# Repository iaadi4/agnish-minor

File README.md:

# pcbassist: prompt-driven PCB design assistant

> **AI-GENERATED DESIGN PLANS ARE NOT VERIFIED FOR FABRICATION.** Everything this tool
> produces must be reviewed and signed off by a qualified electronics engineer before any
> fabrication, assembly or use. The disclaimer is embedded in every output file.

`pcbassist` turns a natural-language hardware requirement into a structured, reviewable
PCB design plan: requirements, architecture, a bill of materials, a pin-level netlist,
electrical and mechanical constraints, a deterministic placement, routing guidance, and
the results of the checks (ERC, power budget, DFM and KiCad DRC). It exports
KiCad 8 files (`.net`, `.kicad_pro`, `.kicad_sch`, `.kicad_pcb`), a BOM CSV and a
`report.md`. A human reviews it through comments, approve/reject/edit/lock decisions and
partial regeneration with a diff, either on the CLI or in a local web UI.

## The core principle: the LLM proposes, deterministic code verifies

| Concern | Owner |
|---|---|
| Interpreting the prompt; assumptions, open questions, conflicts | LLM, output validated against the `Requirements` schema |
| Block architecture | LLM (`Architecture`), coverage checked in code |
| Choosing **every part**, support passives included: a curated MPN, or any of the 21,700 stock KiCad 8 symbols with an exact footprint | LLM (`PartsManifest`) with lookup tools; **every** symbol, footprint and pin-to-pad match checked against the bundled KiCad index |
| The pin-level netlist (`REF.PIN` endpoints, no-connects with reasons, rails) | LLM (`NetlistIntent`) from a pin dossier of real pins; **every** endpoint, pin, short and rail checked, then ERC and the power budget |
| Repairing what the checks find | LLM, in a loop: each submission comes back with the problems to fix until it validates |
| Constraints, IPC-2221 trace widths, outline, holes, placement, routing guidance | **Deterministic** |
| ERC, power budget, DFM, DRC | **Deterministic** Python plus `kicad-cli` |

This "intent engine" follows the design of
[copperhead](https://github.com/copperheadhq/copperhead): the model authors *intent* (parts
and connections), never geometry, and nothing is accepted until deterministic tools agree.
The model never sees an invented pin: its pin dossier, the `symbol_pins` tool and every
validator message come from the KiCad libraries. A part outside the curated library gets
its pins from its KiCad symbol and is flagged `LIB-KICAD-ONLY` (MPN, package match and
ratings unverified); any ratings the model states are flagged `LIB-CLAIMED-RATINGS`.
Datasheet URLs come only from curated data or KiCad symbol metadata, never from the model.

`--engine synth` keeps the original rule-based path: the LLM picks curated MPNs and a
deterministic synthesizer wires them (only the subcircuits it has rules for).

## Quick start

```bash
uv sync
# Offline: hand-authored fixtures stand in for the model (see "Mock mode" below)
uv run pcbassist generate -f examples/iot_env_sensor/prompt.txt --out out/iot --mock-llm
# Live: Anthropic API (model from PCBASSIST_MODEL, default claude-sonnet-5-5)
export ANTHROPIC_API_KEY=...
uv run pcbassist generate "USB-C powered CO2 sensor with an e-paper display" --out out/co2

# Look up what the model can use (the bundled KiCad 8 index)
uv run pcbassist kicad search INA226
uv run pcbassist kicad pins Sensor_Energy:INA226
uv run pcbassist kicad footprint Package_SO:VSSOP-10_3x3mm_P0.5mm
```

`out/iot/` is a **session**:

```
plan.json          latest plan        plan.v1.json, plan.v2.json ...  one file per version
audit.jsonl        every LLM prompt/response and review decision (API keys redacted)
v1/                board.kicad_pcb  board.kicad_sch  board.kicad_pro  board.net
                   bom.csv  report.md  drc.json (when kicad-cli ran)
```

`make demo` generates all five examples plus a refinement into `out/demo/`;
`make serve-demo` opens them in the review UI at http://127.0.0.1:8000.

## Pipeline

```
prompt -> requirements -> architecture -> parts ("components") -> netlist -> constraints
  (LLM)       (LLM)           (LLM + tools, validated)   (LLM + tools, validated + ERC)
                                     ^------ part-level ERC problems loop back ------'
       -> placement -> routing -> checks -> exports
           (rules)      (rules)   ERC/power/DFM/library (+ KiCad DRC on export)
```

**Parts and netlist stages** run as a tool loop on the Anthropic Messages API. The model
can call `search_parts` (curated library), `search_symbols`, `symbol_pins`,
`check_footprints` and `search_footprints` (the KiCad index), and submits with `submit`.
Each submission is parsed with Pydantic and then checked by `pipeline/intent.py`:

* parts: one entry per refdes, value is a value not prose, the block exists, the KiCad
  symbol exists (with "did you mean" / "installed as" suggestions), the footprint exists,
  every symbol pin is a footprint pad, MPN present for active parts, curated parts keep
  their verified symbol and footprint, locked parts stay, rejected parts stay out;
* netlist: every endpoint is a real `REF.PIN` (the error lists the part's pins, or maps
  a pin *name* to its number), no pin in two nets, every pin of every part is in a net or
  a no-connect with a reason, power inputs and grounds are never no-connect, every rail
  has a voltage; then ERC (decoupling, pull-ups, USB-C CC, flyback, LED resistor, driver
  conflicts, supply range, ground pins) and the power budget.

Problems are sent back as `is_error` tool results, up to 5 submissions per stage. Problems
that rewiring cannot fix (a missing decoupling capacitor or pull-up) send the parts stage
round again with that feedback (up to 2 extra rounds). What is still open at the end is
reported as error findings, never dropped. Tool stages are streamed and use automatic
prompt caching.

The requirements and architecture stages put the JSON Schema of their output model in
the system prompt and validate the reply with Pydantic. Unknown keys are rejected (`extra="forbid"`). On a
validation error the errors are sent back and the model retries, up to 3 attempts in
total. A truncated reply counts as invalid. Refusals and API failures surface as typed
`LLMError`s with readable messages.

## Reviewing and iterating

```bash
pcbassist review comment  out/iot -t component:U3 -m "antenna clearance vs enclosure?"
pcbassist review approve  out/iot -t component:U3
pcbassist review lock     out/iot -t component:U2         # kept verbatim on regeneration
pcbassist review reject   out/iot -t component:D2         # avoided on the next refine
pcbassist review edit     out/iot -t placement:R1 --set x_mm=20 --set y_mm=12   # new version
pcbassist refine out/iot --mock-llm -f "Replace the SHT40 with a BME280 so we also get barometric pressure."
pcbassist diff out/iot/plan.v1.json out/iot/plan.v2.json
pcbassist review approve  out/iot -t 'plan:*'             # refuses while checks FAIL (unless --force)
pcbassist check out/iot                                   # exit 1 on FAIL
```

`refine` picks the earliest stage the feedback affects, using deterministic rules:

| Feedback | Restarts at |
|---|---|
| Names a library part, or "replace / instead / swap / use a..." | components |
| "move / place / closer / rotate..." | placement |
| "route / trace / ground plane / stackup..." | routing |
| "60 x 40 mm", "4 layers", "mounting hole", "fab profile" | constraints |
| "connect / wire / pull-up / tie / strap / GPIO / pinout..." | netlist (components with `--engine synth`) |
| Anything else | requirements |

Only that stage and the ones after it are regenerated. Numeric directives (board size,
layer count) are applied directly. Locked and edited parts are carried over and the LLM
is told about them; a rejected MPN is refused by the parts validator, and if the model
proposes it again anyway it stays flagged `rejected` with a `SEL-REJECTED-AGAIN` error. Approvals carry over to parts that did not
change. A locked net that changes produces an error. Each refinement is saved as a new
version, and `diff` reports what changed: parts, nets, rails, outline, moved parts,
findings and the status change.

`pcbassist serve --sessions out` starts a FastAPI app with a single static page: findings,
components with approve/reject/lock/comment buttons, nets, a board view (outline, zones,
antenna keepout, courtyards), the power tree, refinement, a diff between any two versions,
and file downloads. Its REST API is under `/api/sessions/...`.

## Checks

| Group | Rules (finding id prefix) |
|---|---|
| ERC | `ERC-UNCONNECTED` (every pin on a net or an explicit NC with a reason), `ERC-MULTI-NET`, `ERC-NC-CONNECTED`, `ERC-SINGLE-PIN-NET`, `ERC-DRIVER-CONFLICT`, `ERC-POWER-UNDRIVEN`, `ERC-GROUND-PIN`, `ERC-SUPPLY-RANGE`, `ERC-DECOUPLING`, `ERC-I2C-PULLUP`, `ERC-I2C-ADDRESS`, `ERC-USB-ESD`, `ERC-USB-CC`, `ERC-FLOATING-INPUT`, `ERC-FLYBACK`, `ERC-LED-RESISTOR`, `ERC-CAP-VOLTAGE` |
| Power | `PWR-SOURCE`, `PWR-REG-CAPACITY`, `PWR-DROPOUT`, `PWR-REG-INPUT`, `PWR-THERMAL`, `PWR-CHARGE-RATE`, `PWR-BATTERY-LIFE`, `PWR-NO-DATA` |
| DFM / placement | `DFM-PASSIVE-SIZE`, `DFM-PAD-PITCH`, `DFM-DRILL`, `DFM-THT`, `DFM-BGA`, `DFM-NETCLASS`, `DFM-COURTYARD-OVERLAP`, `DFM-OUTSIDE-BOARD`, `DFM-EDGE-CLEARANCE`, `DFM-KEEPOUT`, `DFM-UNPLACED`, `DFM-DECOUPLING-DISTANCE`, `DFM-CONNECTOR-EDGE`, `DFM-MIXED-ASSEMBLY` |
| Library | `LIB-UNVERIFIED`, `LIB-FOOTPRINT`, `LIB-LOW-CONFIDENCE`, `LIB-NO-DATASHEET` |
| KiCad DRC | `DRC-<type>` from `kicad-cli pcb drc`. Unrouted connections and silkscreen findings are expected on an unrouted, auto-placed board, so they are reported as info. Errors that lie entirely inside one library footprint (for example a module's 0.2 mm thermal vias) are reported as warnings. |

Status is `PASS`, `PASS_WITH_WARNINGS` or `FAIL` (any error).

### KiCad DRC

DRC runs during export when `kicad-cli` is available, either from
`PCBASSIST_KICAD_CLI` or from `kicad-cli` on `PATH`. Without KiCad installed:

```bash
export PCBASSIST_KICAD_CLI=$PWD/scripts/kicad-cli-docker   # runs kicad/kicad:8.0.9 in Docker
make test-kicad   # real DRC, plus KiCad's netlist from our schematic compared with the plan's
```

The `Dockerfile` builds on the official KiCad 8 image, so `kicad-cli` is always there:

```bash
docker build -t pcbassist .
docker run --rm -v "$PWD/out:/work/out" pcbassist generate \
  -f /opt/pcbassist/examples/relay_motor_12v/prompt.txt --out out/relay --mock-llm
docker run --rm -p 8000:8000 -v "$PWD/sessions:/work/sessions" pcbassist serve --host 0.0.0.0
```

## Examples

Committed in `examples/<name>/` (prompt and full session output). Regenerate with
`make examples`.

| Example | What it shows | Status |
|---|---|---|
| `iot_env_sensor` | ESP32-C3, USB-C + LiPo charger, LDO, SHT40, battery sense; plus a **v2 refinement** (SHT40 → BME280, see `out/diff_v1_v2.txt`) | PASS_WITH_WARNINGS (thin battery-life margin, LDO dropout at low battery, VBUS at its 500 mA limit) |
| `ble_coin_tag` | nRF52832 module on a CR2032, LIS3DH wake-on-motion, Tag-Connect SWD | PASS_WITH_WARNINGS |
| `relay_motor_12v` | 12 V input with fuse, series diode and TVS; LM2596 buck; LDO; ESP32; DRV8871 H-bridge; relay with FET + flyback; screw terminals; 4 M3 holes | PASS_WITH_WARNINGS |
| `motor_current_monitor` | `relay_motor_12v` plus an **INA226** high-side current monitor on the motor supply. The INA226 is not in the curated library: it comes from the KiCad symbol `Sensor_Energy:INA226` and is wired pin by pin (shunt, VBUS sense, I2C with pull-ups, address straps, decoupling) | PASS_WITH_WARNINGS (`LIB-KICAD-ONLY` for the INA226) |
| `flawed_coin_wifi` | **Intentionally flawed:** Wi-Fi on a coin cell, 3.3 V LDO from 3 V, 5 V relay on 3.3 V, two identical I2C sensors, 15 x 15 mm board, an off-library transistor left unwired | **FAIL**: 14 errors (I2C address clash, supply range, dropout, regulator capacity, source capacity, battery life, board too small...) |

## Mock mode and honesty notes

* **Mock fixtures are not recordings.** The requirements, architecture and (synth-engine)
  selection fixtures are hand-authored; the parts and netlist fixtures are *derived* from
  the synthesizer's design for each example (`scripts/derive_intent_fixtures.py`), plus a
  hand-written INA226 addition for `motor_current_monitor`. Mock mode pushes them through
  the same validators, ERC repair loop and downstream stages as a live run.
* **Mock fixtures in general**: No API key was available while
  this was built. They live in `fixtures/llm/<stage>/<example>.json`, are generated from
  `scripts/author_fixtures.py`, and are written in exactly the JSON shape the live model is
  asked for. Lookup order is an exact prompt hash, then keyword match, then `_default`. A
  non-exact match adds a `MOCK-NEAREST` warning, because the plan then describes the
  nearest example, not your prompt. `generate --record-fixtures DIR` saves live answers as
  new fixtures.
* The live Anthropic path (including the streamed tool loop) is tested against a faked
  SDK client only.
* **KiCad index:** `data/kicad/symbol_index.json.gz` and `footprint_geom.json.gz` (3.6 MB)
  hold every stock KiCad 8.0.9 symbol's pins and every footprint's pads and courtyard,
  built by `scripts/build_kicad_index.py`. Exported boards embed the real footprint file
  when a KiCad library tree is available (`make kicad-libs` copies it out of the Docker
  image), and otherwise a footprint rebuilt from the index (pads + courtyard; KiCad's
  *Update Footprints from Library* restores the graphics).
* **Pin tables** come from the official KiCad symbol libraries. Each pin is cross-checked
  against a pad of the KiCad footprint at seed-build time (`scripts/build_seed.py`). No IC
  pin table was typed by hand. Pins are still the KiCad community's data: verify against
  the datasheet.
* Electrical limits, currents and specs in `data/parts_curated.toml` are curated values
  with a `data_confidence` level. Design rules of thumb (regulator capacitors, ESP32
  strapping pull-ups, DRV8871 ILIM) are in `pipeline/synth.py`, each with its reasoning
  and a "verify" note.
* Relay NO/NC contacts and barrel-jack polarity are not asserted. The report asks the
  engineer to confirm them.

## Configuration

| Variable | Meaning |
|---|---|
| `ANTHROPIC_API_KEY` | Live mode (never logged; redacted in the audit trail) |
| `PCBASSIST_MODEL` | Model id (default `claude-sonnet-5-5`) |
| `PCBASSIST_LLM_FALLBACKS` | `off` disables server-side fallback models |
| `PCBASSIST_LLM_EFFORT` | Optional effort setting passed to the API |
| `PCBASSIST_KICAD_CLI` | Path to `kicad-cli` (or `scripts/kicad-cli-docker`) |
| `PCBASSIST_KICAD_FOOTPRINT_DIR` | KiCad footprint tree for full footprint files (`none` disables) |
| `PCBASSIST_SYMBOL_INDEX`, `PCBASSIST_FOOTPRINT_INDEX` | Override the bundled KiCad index files |
| `PCBASSIST_DATA_DIR`, `PCBASSIST_FIXTURES_DIR` | Override the bundled data / fixtures |

## Development

```bash
make check-all     # ruff, ruff format --check, mypy --strict (core modules), pytest + 80% coverage, library validate
make test-kicad    # the two tests that need real KiCad
make seed          # rebuild the component library from KiCad sources (network)
make fixtures      # regenerate mock fixtures (hand-authored + derived parts/netlist)
make kicad-libs    # copy KiCad 8.0.9 libraries out of Docker into ~/.cache/pcbassist
make kicad-index   # rebuild the bundled symbol/footprint index from them
```

Layout: `schemas/` (Pydantic models + JSON Schema export), `llm/` (client, mock,
structured retry, audit), `library/` (SQLite library, footprint resolver), `kicad/`
(S-expression I/O, footprint geometry), `pipeline/` (stages, synthesizer, constraints,
placement, routing, engine), `checks/`, `export/`, `review/` (sessions, decisions,
refine, diff), `ui/` (FastAPI and a static page). Design decisions and the milestone log
are in [PLAN.md](PLAN.md).

## Known limitations

* No routing (only the ratsnest), single-sided placement and 0° rotations. Edge
  connectors still need rotating so the mating face points off the board.
* The schematic is one flat sheet of generated box symbols with net labels. It is
  correct by construction (KiCad's netlist from it matches the plan) but not a
  hand-drawn schematic.
* The intent engine's quality depends on the model: the validators guarantee that every
  part and pin exists and that ERC/power rules pass, not that the circuit is the best one.
  Ratings of parts outside the curated library are the model's datasheet claims.
* With `--engine synth`, subcircuits exist only for the parts the rules cover (ESP32/nRF52
  modules, MCP73831, fixed LDOs, LM2596-5.0, I2C sensors, USB-C, relays, DRV8871, LEDs,
  buttons, SWD/UART/Qwiic headers, input protection); other parts get power and ground
  only, with a `SYNTH-INCOMPLETE` warning.
* The fab profiles are generic and conservative, not any specific fab's published rules.
* Mains, safety and RF certification are out of scope.

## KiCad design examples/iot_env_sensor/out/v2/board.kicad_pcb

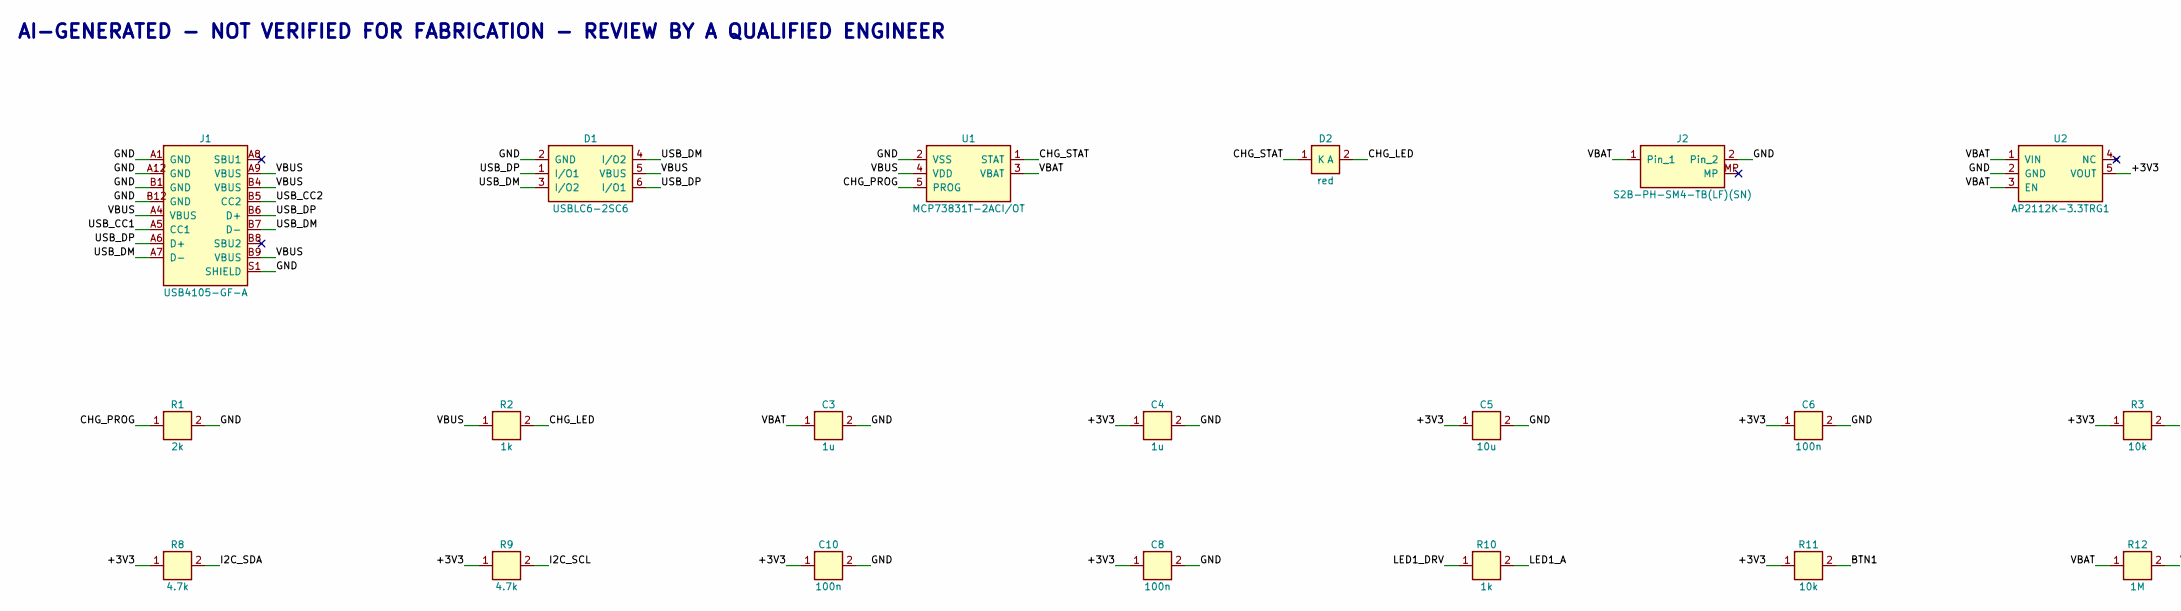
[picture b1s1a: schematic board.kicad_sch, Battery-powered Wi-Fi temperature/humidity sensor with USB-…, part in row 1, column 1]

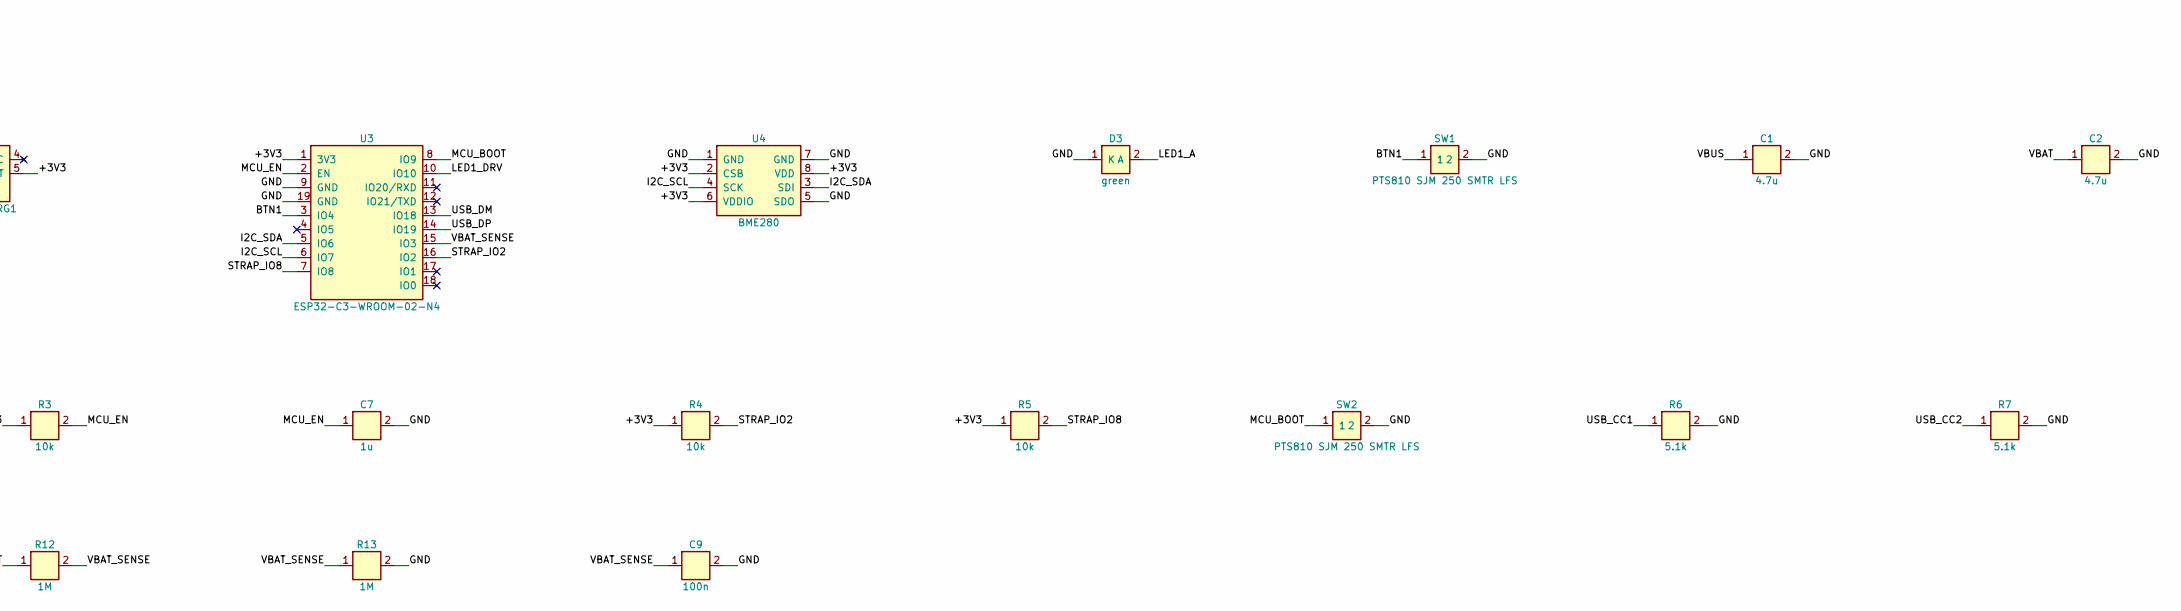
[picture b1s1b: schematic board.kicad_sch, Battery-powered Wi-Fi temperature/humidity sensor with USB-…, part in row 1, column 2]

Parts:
C1, C2: 4.7u; C_0603_1608Metric; MPN GRM188R61A475KE15D
C3, C4, C7: 1u; C_0402_1005Metric; MPN GRM155R61A105KE15D
C5: 10u; C_0603_1608Metric; MPN GRM188R61A106KE69D
C6, C8, C9, C10: 100n; C_0402_1005Metric; MPN GRM155R71C104KA88D
D1: USBLC6-2SC6; SOT-23-6; MPN USBLC6-2SC6
D2: red; LED_0603_1608Metric; MPN LTST-C191KRKT
D3: green; LED_0603_1608Metric; MPN LTST-C191KGKT
J1: USB4105-GF-A; USB_C_Receptacle_GCT_USB4105-xx-A_16P_TopMnt_Horizontal; MPN USB4105-GF-A
J2: S2B-PH-SM4-TB(LF)(SN); JST_PH_S2B-PH-SM4-TB_1x02-1MP_P2.00mm_Horizontal; MPN S2B-PH-SM4-TB(LF)(SN)
R1: 2k; R_0603_1608Metric; MPN RC0603FR-072KL
R2, R10: 1k; R_0402_1005Metric; MPN RC0402FR-071KL
R3, R4, R5, R11: 10k; R_0402_1005Metric; MPN RC0402FR-0710KL
R6, R7: 5.1k; R_0402_1005Metric; MPN RC0402FR-075K1L
R8, R9: 4.7k; R_0402_1005Metric; MPN RC0402FR-074K7L
R12, R13: 1M; R_0402_1005Metric; MPN RC0402FR-071ML
SW1, SW2: PTS810 SJM 250 SMTR LFS; SW_SPST_PTS810; MPN PTS810 SJM 250 SMTR LFS
U1: MCP73831T-2ACI/OT; SOT-23-5; MPN MCP73831T-2ACI/OT
U2: AP2112K-3.3TRG1; SOT-23-5; MPN AP2112K-3.3TRG1
U3: ESP32-C3-WROOM-02-N4; ESP32-C3-WROOM-02; MPN ESP32-C3-WROOM-02-N4
U4: BME280; Bosch_LGA-8_2.5x2.5mm_P0.65mm_ClockwisePinNumbering; MPN BME280

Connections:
+3V3: C4.1, C5.1, C6.1, C8.1, C10.1, R3.1, R4.1, R5.1, R8.1, R9.1, R11.1, U2.5 (VOUT), U3.1 (3V3), U4.2 (CSB), U4.6 (VDDIO), U4.8 (VDD)
BTN1: R11.2, SW1.1, U3.3 (IO4)
CHG_LED: D2.2 (A), R2.2
CHG_PROG: R1.1, U1.5 (PROG)
CHG_STAT: D2.1 (K), U1.1 (STAT)
GND: C1.2, C2.2, C3.2, C4.2, C5.2, C6.2, C7.2, C8.2, C9.2, C10.2, D1.2 (GND), D3.1 (K), J1.A1 (GND), J1.A12 (GND), J1.B1 (GND), J1.B12 (GND), J1.S1 (SHIELD), J2.2, R1.2, R6.2, R7.2, R13.2, SW1.2, SW2.2, U1.2 (VSS), U2.2 (GND), U3.9 (GND), U3.19 (GND), U4.1 (GND), U4.5 (SDO), U4.7 (GND)
I2C_SCL: R9.2, U3.6 (IO7), U4.4 (SCK)
I2C_SDA: R8.2, U3.5 (IO6), U4.3 (SDI)
LED1_A: D3.2 (A), R10.2
LED1_DRV: R10.1, U3.10 (IO10)
MCU_BOOT: SW2.1, U3.8 (IO9)
MCU_EN: C7.1, R3.2, U3.2 (EN)
STRAP_IO2: R4.2, U3.16 (IO2)
STRAP_IO8: R5.2, U3.7 (IO8)
USB_CC1: J1.A5 (CC1), R6.1
USB_CC2: J1.B5 (CC2), R7.1
USB_DM: D1.3 (I/O2), D1.4 (I/O2), J1.A7 (D-), J1.B7 (D-), U3.13 (IO18)
USB_DP: D1.1 (I/O1), D1.6 (I/O1), J1.A6 (D+), J1.B6 (D+), U3.14 (IO19)
VBAT: C2.1, C3.1, J2.1, R12.1, U1.3 (VBAT), U2.1 (VIN), U2.3 (EN)
VBAT_SENSE: C9.1, R12.2, R13.1, U3.15 (IO3)
VBUS: C1.1, D1.5 (VBUS), J1.A4 (VBUS), J1.A9 (VBUS), J1.B4 (VBUS), J1.B9 (VBUS), R2.1, U1.4 (VDD)

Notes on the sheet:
AI-GENERATED - NOT VERIFIED FOR FABRICATION - REVIEW BY A QUALIFIED ENGINEER

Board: 2 copper layers, 34 parts (0 on the bottom side), 21 nets, no tracks yet.

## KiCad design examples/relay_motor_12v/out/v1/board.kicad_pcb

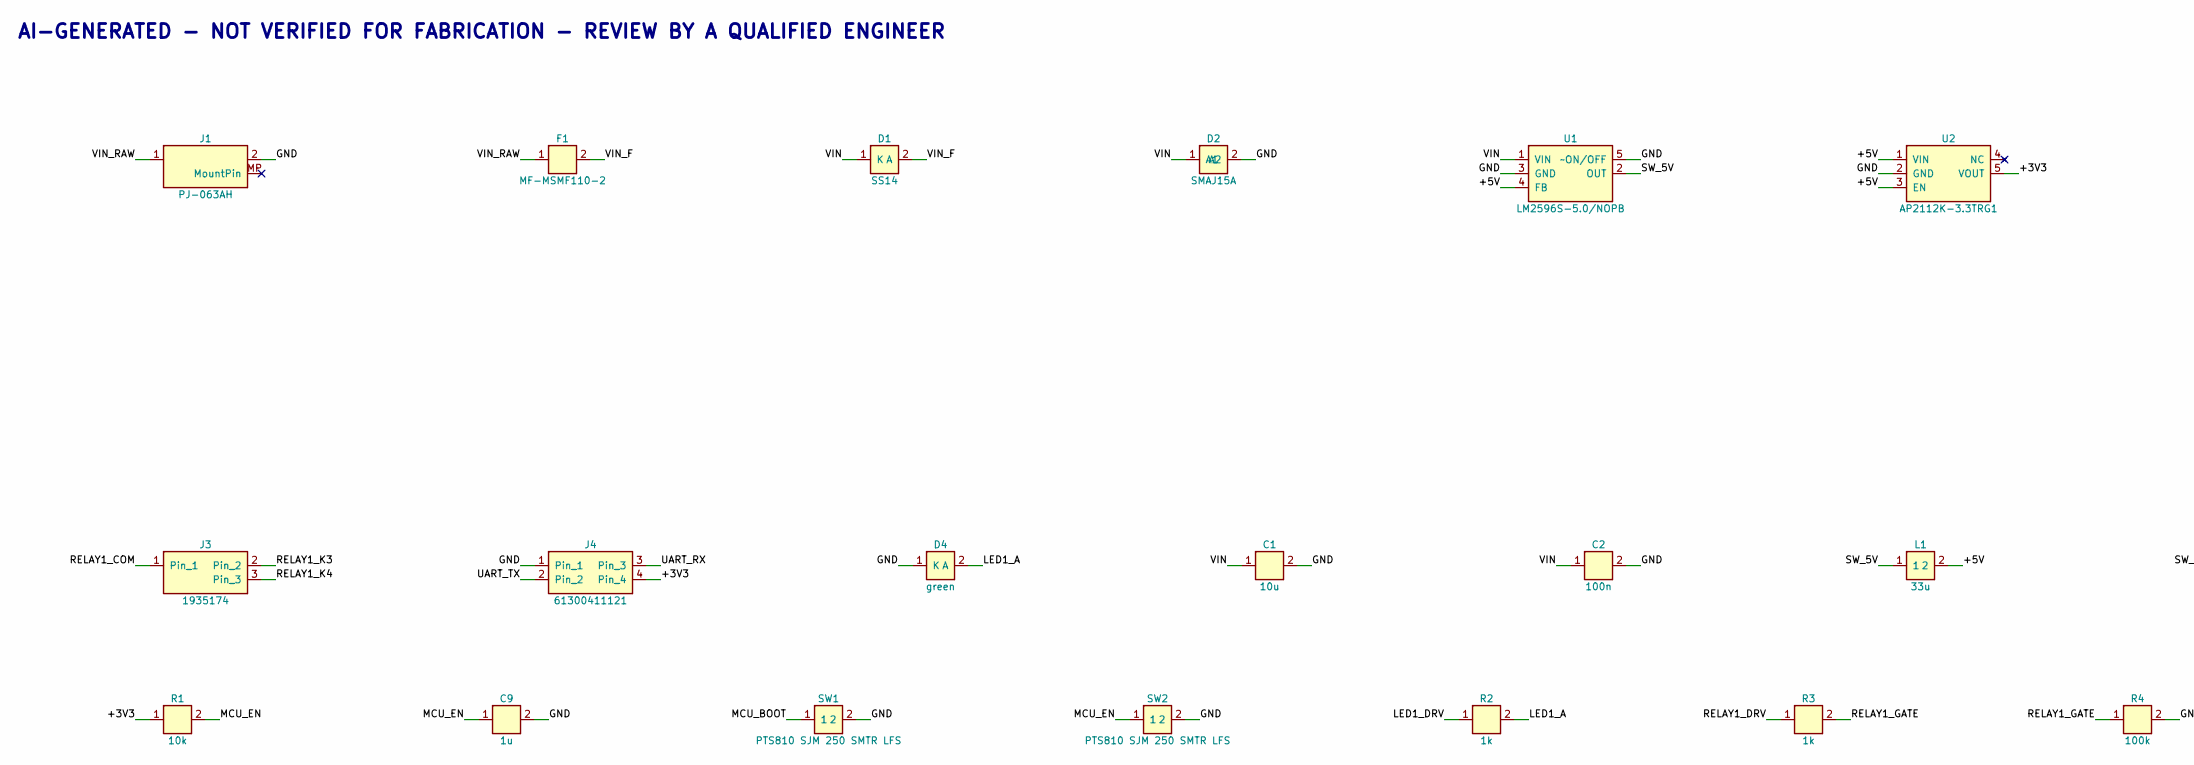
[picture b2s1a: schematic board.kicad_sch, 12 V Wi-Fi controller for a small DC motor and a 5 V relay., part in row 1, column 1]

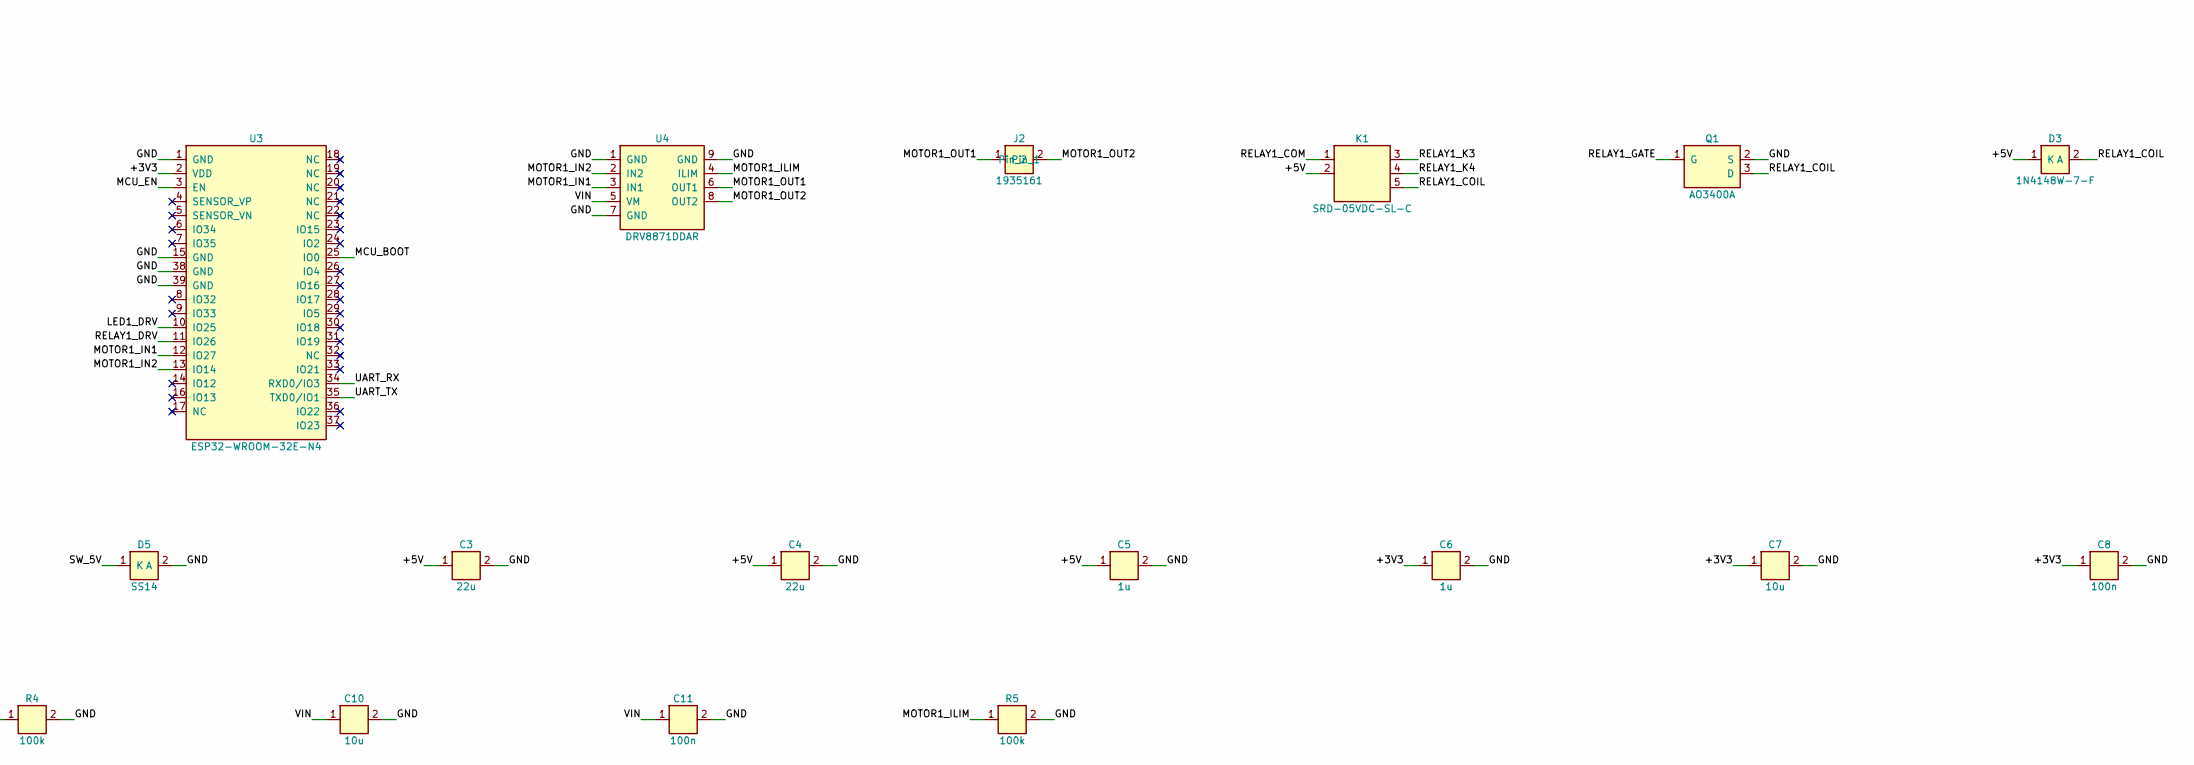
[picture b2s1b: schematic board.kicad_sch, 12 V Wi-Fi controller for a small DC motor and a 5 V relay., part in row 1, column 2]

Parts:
C1, C10: 10u; C_0805_2012Metric; MPN GRM21BR61E106KA73L
C2, C11: 100n; C_0603_1608Metric; MPN GRM188R71H104KA93D
C3, C4: 22u; C_0805_2012Metric; MPN GRM21BR61C226ME44L
C5, C6, C9: 1u; C_0402_1005Metric; MPN GRM155R61A105KE15D
C7: 10u; C_0603_1608Metric; MPN GRM188R61A106KE69D
C8: 100n; C_0402_1005Metric; MPN GRM155R71C104KA88D
D1, D5: SS14; D_SMA; MPN SS14
D2: SMAJ15A; D_SMA; MPN SMAJ15A
D3: 1N4148W-7-F; D_SOD-123; MPN 1N4148W-7-F
D4: green; LED_0603_1608Metric; MPN LTST-C191KGKT
F1: MF-MSMF110-2; Fuse_1812_4532Metric; MPN MF-MSMF110-2
J1: PJ-063AH; BarrelJack_CUI_PJ-063AH_Horizontal; MPN PJ-063AH
J2: 1935161; TerminalBlock_Phoenix_MKDS-1,5-2-5.08_1x02_P5.08mm_Horizont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; MPN 1935161
J3: 1935174; TerminalBlock_Phoenix_MKDS-1,5-3-5.08_1x03_P5.08mm_Horizont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; MPN 1935174
J4: 61300411121; PinHeader_1x04_P2.54mm_Vertical; MPN 61300411121
K1: SRD-05VDC-SL-C; Relay_SPDT_SANYOU_SRD_Series_Form_C; MPN SRD-05VDC-SL-C
L1: 33u; L_Bourns_SRN8040TA; MPN SRN8040TA-330M
Q1: AO3400A; SOT-23; MPN AO3400A
R1: 10k; R_0402_1005Metric; MPN RC0402FR-0710KL
R2, R3: 1k; R_0402_1005Metric; MPN RC0402FR-071KL
R4, R5: 100k; R_0402_1005Metric; MPN RC0402FR-07100KL
SW1, SW2: PTS810 SJM 250 SMTR LFS; SW_SPST_PTS810; MPN PTS810 SJM 250 SMTR LFS
U1: LM2596S-5.0/NOPB; TO-263-5_TabPin3; MPN LM2596S-5.0/NOPB
U2: AP2112K-3.3TRG1; SOT-23-5; MPN AP2112K-3.3TRG1
U3: ESP32-WROOM-32E-N4; ESP32-WROOM-32E; MPN ESP32-WROOM-32E-N4
U4: DRV8871DDAR; Texas_HTSOP-8-1EP_3.9x4.9mm_P1.27mm_EP2.95x4.9mm_Mask2.4x3.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; MPN DRV8871DDAR

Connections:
+3V3: C6.1, C7.1, C8.1, J4.4, R1.1, U2.5 (VOUT), U3.2 (VDD)
+5V: C3.1, C4.1, C5.1, D3.1 (K), K1.2, L1.2, U1.4 (FB), U2.1 (VIN), U2.3 (EN)
GND: C1.2, C2.2, C3.2, C4.2, C5.2, C6.2, C7.2, C8.2, C9.2, C10.2, C11.2, D2.2 (A2), D4.1 (K), D5.2 (A), J1.2, J4.1, Q1.2 (S), R4.2, R5.2, SW1.2, SW2.2, U1.3 (GND), U1.5 (~ON/OFF), U2.2 (GND), U3.1 (GND), U3.15 (GND), U3.38 (GND), U3.39 (GND), U4.1 (GND), U4.7 (GND), U4.9 (GND)
LED1_A: D4.2 (A), R2.2
LED1_DRV: R2.1, U3.10 (IO25)
MCU_BOOT: SW1.1, U3.25 (IO0)
MCU_EN: C9.1, R1.2, SW2.1, U3.3 (EN)
MOTOR1_ILIM: R5.1, U4.4 (ILIM)
MOTOR1_IN1: U3.12 (IO27), U4.3 (IN1)
MOTOR1_IN2: U3.13 (IO14), U4.2 (IN2)
MOTOR1_OUT1: J2.1, U4.6 (OUT1)
MOTOR1_OUT2: J2.2, U4.8 (OUT2)
RELAY1_COIL: D3.2 (A), K1.5, Q1.3 (D)
RELAY1_COM: J3.1, K1.1
RELAY1_DRV: R3.1, U3.11 (IO26)
RELAY1_GATE: Q1.1 (G), R3.2, R4.1
RELAY1_K3: J3.2, K1.3
RELAY1_K4: J3.3, K1.4
SW_5V: D5.1 (K), L1.1, U1.2 (OUT)
UART_RX: J4.3, U3.34 (RXD0/IO3)
UART_TX: J4.2, U3.35 (TXD0/IO1)
VIN: C1.1, C2.1, C10.1, C11.1, D1.1 (K), D2.1 (A1), U1.1 (VIN), U4.5 (VM)
VIN_F: D1.2 (A), F1.2
VIN_RAW: F1.1, J1.1

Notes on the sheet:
AI-GENERATED - NOT VERIFIED FOR FABRICATION - REVIEW BY A QUALIFIED ENGINEER

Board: 2 copper layers, 39 parts (0 on the bottom side), 24 nets, no tracks yet.

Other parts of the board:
H1, H2, H3, H4: MOUNTING-HOLE-M3; MountingHole_3.2mm_M3

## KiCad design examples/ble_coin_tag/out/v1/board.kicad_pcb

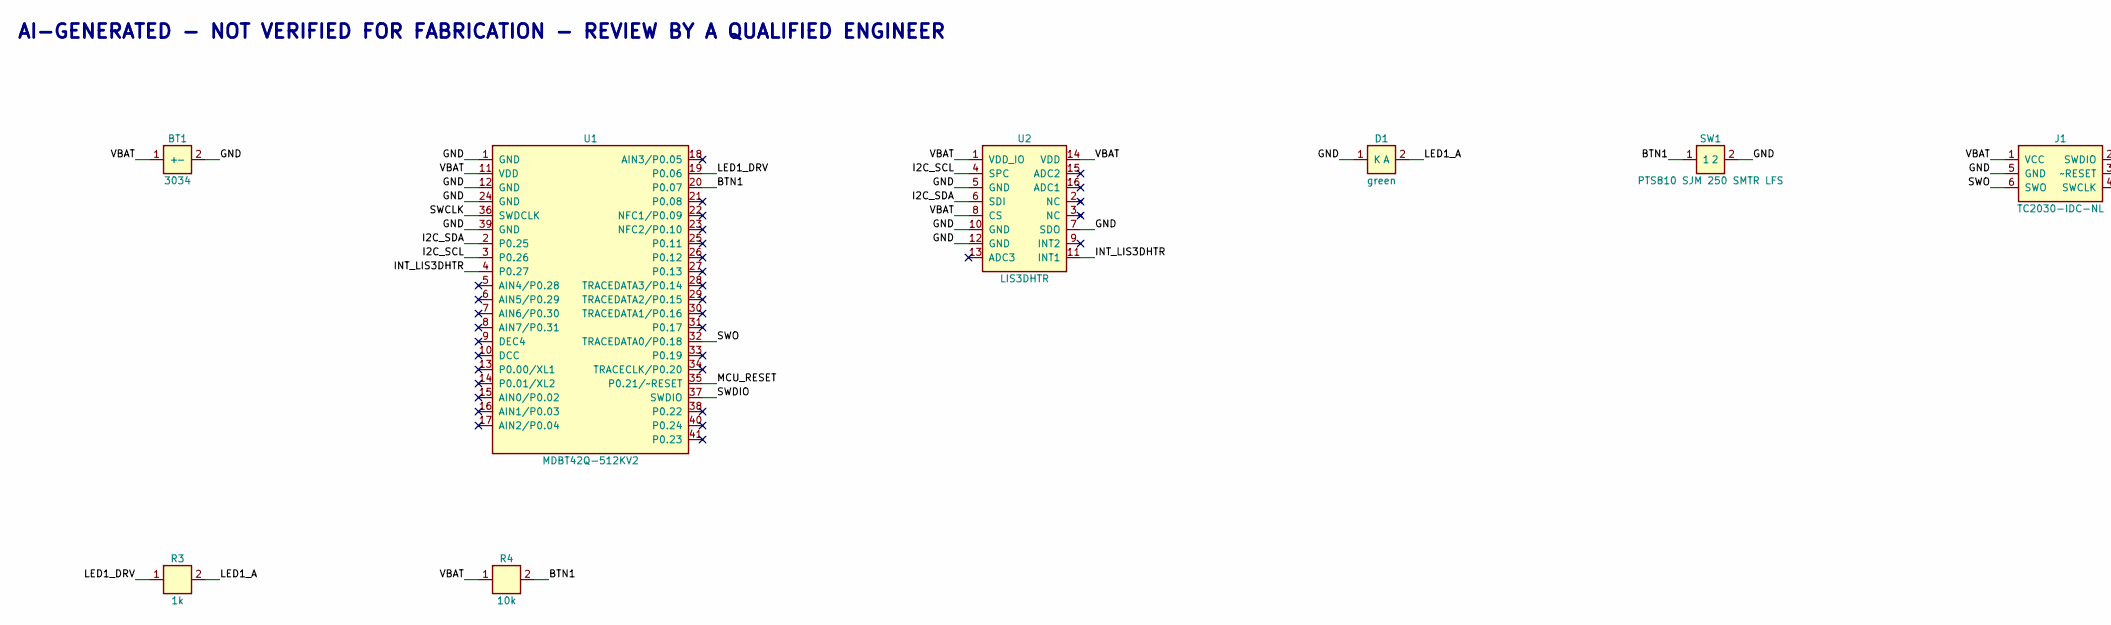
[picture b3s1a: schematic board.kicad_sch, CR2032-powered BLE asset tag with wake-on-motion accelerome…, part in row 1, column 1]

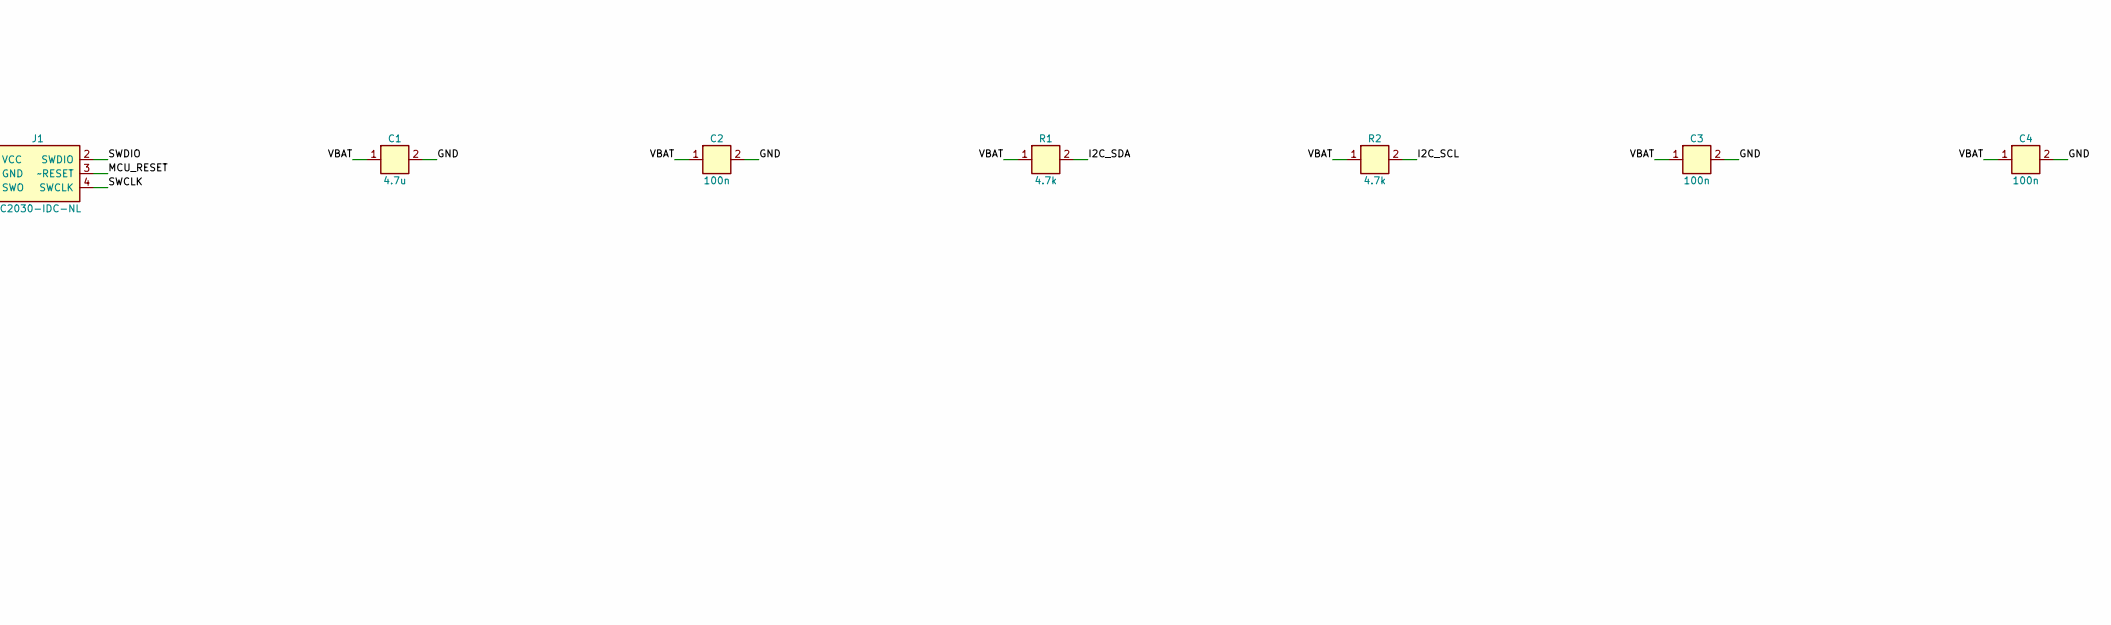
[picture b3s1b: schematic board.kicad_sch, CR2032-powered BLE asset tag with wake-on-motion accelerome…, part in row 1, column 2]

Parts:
BT1: 3034; BatteryHolder_Keystone_3034_1x20mm; MPN 3034
C1: 4.7u; C_0603_1608Metric; MPN GRM188R61A475KE15D
C2, C3, C4: 100n; C_0402_1005Metric; MPN GRM155R71C104KA88D
D1: green; LED_0603_1608Metric; MPN LTST-C191KGKT
J1: TC2030-IDC-NL; Tag-Connect_TC2030-IDC-NL_2x03_P1.27mm_Vertical; MPN TC2030-IDC-NL
R1, R2: 4.7k; R_0402_1005Metric; MPN RC0402FR-074K7L
R3: 1k; R_0402_1005Metric; MPN RC0402FR-071KL
R4: 10k; R_0402_1005Metric; MPN RC0402FR-0710KL
SW1: PTS810 SJM 250 SMTR LFS; SW_SPST_PTS810; MPN PTS810 SJM 250 SMTR LFS
U1: MDBT42Q-512KV2; Raytac_MDBT42Q; MPN MDBT42Q-512KV2
U2: LIS3DHTR; LGA-16_3x3mm_P0.5mm_LayoutBorder3x5y; MPN LIS3DHTR

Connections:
BTN1: R4.2, SW1.1, U1.20 (P0.07)
GND: BT1.2 (-), C1.2, C2.2, C3.2, C4.2, D1.1 (K), J1.5 (GND), SW1.2, U1.1 (GND), U1.12 (GND), U1.24 (GND), U1.39 (GND), U2.5 (GND), U2.7 (SDO), U2.10 (GND), U2.12 (GND)
I2C_SCL: R2.2, U1.3 (P0.26), U2.4 (SPC)
I2C_SDA: R1.2, U1.2 (P0.25), U2.6 (SDI)
INT_LIS3DHTR: U1.4 (P0.27), U2.11 (INT1)
LED1_A: D1.2 (A), R3.2
LED1_DRV: R3.1, U1.19 (P0.06)
MCU_RESET: J1.3 (~RESET), U1.35 (P0.21/~RESET)
SWCLK: J1.4 (SWCLK), U1.36 (SWDCLK)
SWDIO: J1.2 (SWDIO), U1.37 (SWDIO)
SWO: J1.6 (SWO), U1.32 (TRACEDATA0/P0.18)
VBAT: BT1.1 (+), C1.1, C2.1, C3.1, C4.1, J1.1 (VCC), R1.1, R2.1, R4.1, U1.11 (VDD), U2.1 (VDD_IO), U2.8 (CS), U2.14 (VDD)

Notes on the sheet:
AI-GENERATED - NOT VERIFIED FOR FABRICATION - REVIEW BY A QUALIFIED ENGINEER

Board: 2 copper layers, 14 parts (0 on the bottom side), 12 nets, no tracks yet.

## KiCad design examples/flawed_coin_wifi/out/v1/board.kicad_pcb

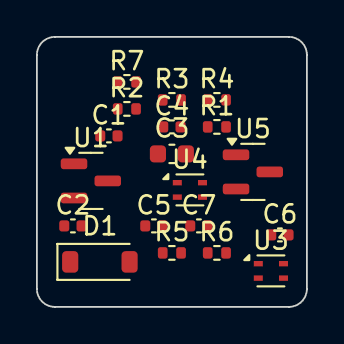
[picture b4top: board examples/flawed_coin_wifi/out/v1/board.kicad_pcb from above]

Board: 2 copper layers, 15.0 x 15.0 mm, 19 parts (0 on the bottom side), 7 nets, no tracks yet.

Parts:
C1, C2, C5: 1u; C_0402_1005Metric
C3: 10u; C_0603_1608Metric
C4, C6, C7: 100n; C_0402_1005Metric
D1: 1N4148W-7-F; D_SOD-123
R1, R2, R3: 10k; R_0402_1005Metric
R4, R5: 4.7k; R_0402_1005Metric
R6: 1k; R_0402_1005Metric
R7: 100k; R_0402_1005Metric
U1: MCP1700T-3302E/TT; SOT-23
U3, U4: SHT40-AD1B-R3; Sensirion_DFN-4_1.5x1.5mm_P0.8mm_SHT4x_NoCentralPad
U5: MMBT3904; SOT-23

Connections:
+3V3: C2.1, C3.1, C4.1, C6.1, C7.1, D1.1, R1.1, R2.1, R3.1, R4.1, R5.1, U1.2, U3.3, U4.3
GND: C1.2, C2.2, C3.2, C4.2, C5.2, C6.2, C7.2, R7.2, U1.1, U3.4, U4.4
I2C_SCL: R5.2, U3.2, U4.2
I2C_SDA: R4.2, U3.1, U4.1
MCU_EN: C5.1, R1.2
RELAY1_GATE: R6.2, R7.1
VBAT: C1.1, U1.3

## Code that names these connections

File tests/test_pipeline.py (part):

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    mcu = _ref(plan, "ESP32-C3-WROOM-02-N4")
    pins = _pins_of(plan, mcu)
    assert pins["1"] == "+3V3" and pins["9"] == "GND"
    assert pins["14"] == "USB_DP" and pins["13"] == "USB_DM"
    assert pins["2"] == "MCU_EN"
    # decoupling caps are tied to the MCU supply pin
    dec = [c for c in plan.components if c.support_for == mcu and c.role.startswith("Decoupling")]
    assert {c.value for c in dec} == {"10u", "100n"}
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    mcu = _ref(plan, "MDBT42Q-512KV2")
    pins = _pins_of(plan, mcu)
    assert pins["11"] == "VBAT"
    assert pins["36"] == "SWCLK" and pins["37"] == "SWDIO" and pins["35"] == "MCU_RESET"
    acc = _ref(plan, "LIS3DHTR")
    apins = _pins_of(plan, acc)
    assert apins["8"] == "VBAT"  # CS high selects I2C
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    assert fuse == {"1": "VIN_RAW", "2": "VIN_F"}
    diode = plan.component(_ref(plan, "SS14"))
    assert diode is not None and diode.origin == "llm"
    assert _pins_of(plan, diode.ref_des) == {"2": "VIN_F", "1": "VIN"}
    relay = _ref(plan, "SRD-05VDC-SL-C")
    rp = _pins_of(plan, relay)
    assert rp["2"] == "+5V" and rp["5"] == "RELAY1_COIL"
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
